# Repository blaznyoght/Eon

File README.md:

Eon
===

Electronic schematics work, ltspice, ngpsice, geda related

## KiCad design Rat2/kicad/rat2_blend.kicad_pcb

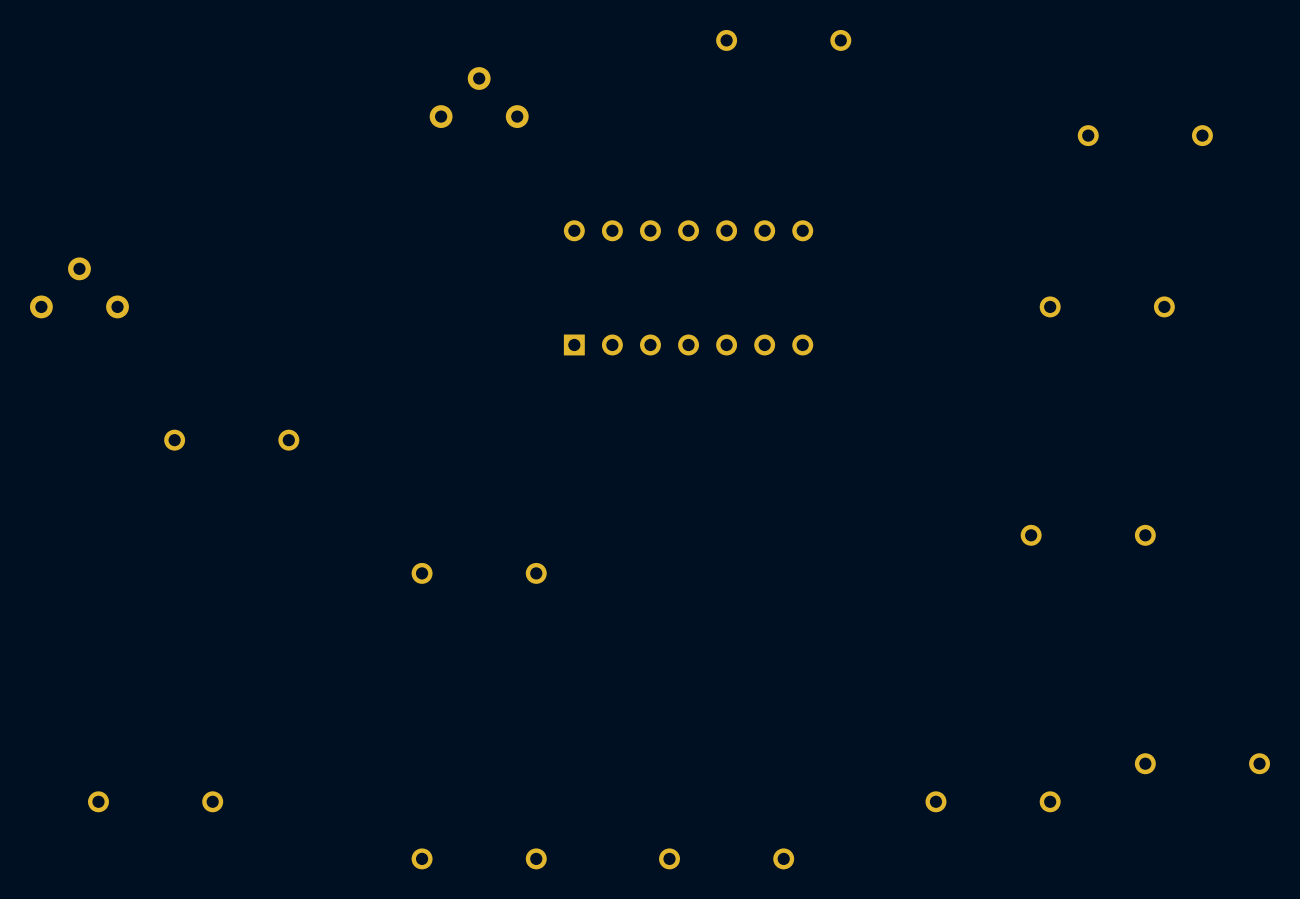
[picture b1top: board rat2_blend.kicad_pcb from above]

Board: 2 copper layers, 14 parts (0 on the bottom side), 8 nets, no tracks yet.

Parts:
C8, C15: 330n; R3
C16: 4.7u; R3
C17: 47n; R3
R14, R15: 1k; R3
R16: 33k; R3
R17: 22k; R3
R18, R19: 10k; R3
R20: 47k; R3
RV4_LPF1, RV5_LPF1: 250k; RV2
U1: TL074; DIP-14__300

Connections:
unnamed: C15.2, RV5_LPF1.2, U1.5
unnamed: R16.1, R17.1, U1.6
unnamed: C8.1, R15.1, RV4_LPF1.2
unnamed: R14.1, U1.1, U1.2
unnamed: R19.1, U1.10
unnamed: C16.1, U1.8
unnamed: C17.2, R20.1, U1.9
unnamed: C8.2, C17.1, R18.1, U1.7

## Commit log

2014-05-05 Initialisation: - big muff - tech21 - capacitancemeter
2014-05-12 Nouveaux projets
2014-05-12 Screamer schematic
2014-05-13 Screamer
2014-05-15 deuxieme essai schema Screamer TG
2014-05-16 Screamer final
2014-05-16 new !
2014-05-21 New models
2014-05-25 rat2
2014-05-29 Oscillo
2014-05-30 essai de filtre crossover
2014-06-02 tests filtres
2014-06-05 bigmuzz
2014-06-05 more...
2014-06-05 CrossOver bg
2014-06-06 tests
2014-07-17 new schemes
2014-07-18 rat2 with LM308A, blend and nohp
2014-07-23 Rat2 with blended lp
2014-08-20 LPF avec dephaseur
2014-09-28 Many
2014-09-29 rat2 lpf progress
2014-10-02 schematics
